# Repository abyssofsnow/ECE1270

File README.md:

# ECE1270

555 Timer Project built using Eagle Software

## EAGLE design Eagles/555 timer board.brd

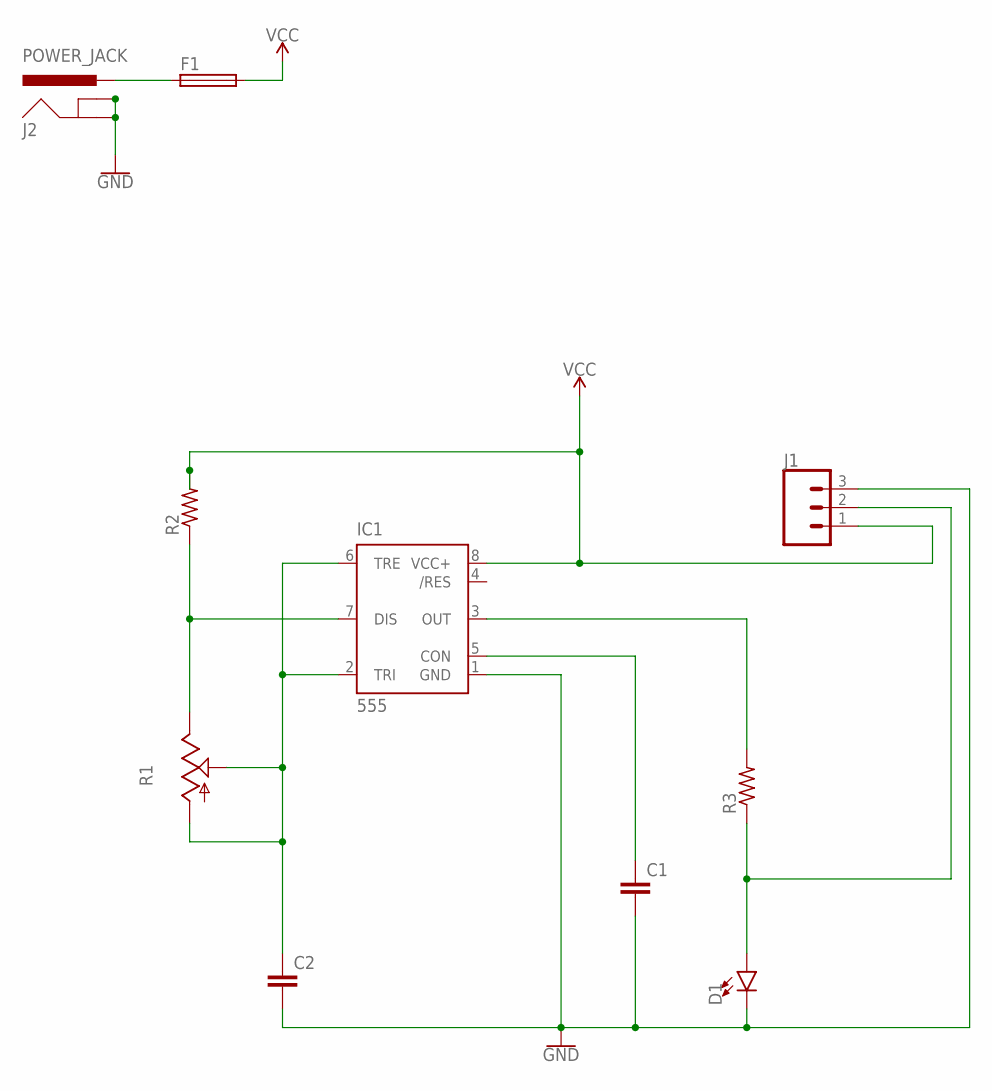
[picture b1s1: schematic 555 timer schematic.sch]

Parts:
C1: C7.5/3; C7.5B3
C2: C15/5; C15B5
D1: LED5MM; LED_5MM
F1: SH22
IC1: 555; DIP08
J1: CONN_03; 1X03
J2: POWER_JACK; POWER_JACK_PTH
R1: TRIM_US-CA6V; CA6V
R2: R-US_R1210; R1210
R3: R-US_0207/12; 0207/12

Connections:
GND: C1.2, C2.2, D1.K (C), IC1.1 (GND), J1.3
unnamed: F1.1, J2.PWR
unnamed: J2.GND, J2.GNDBREAK
unnamed: C2.1, IC1.2 (TRI), IC1.6 (TRE), R1.A, R1.S
unnamed: IC1.7 (DIS), R1.E, R2.1
unnamed: C1.1, IC1.5 (CON)
unnamed: D1.A, J1.2, R3.1
unnamed: IC1.3 (OUT), R3.2
VCC: F1.2, IC1.8 (VCC+), J1.1, R2.2

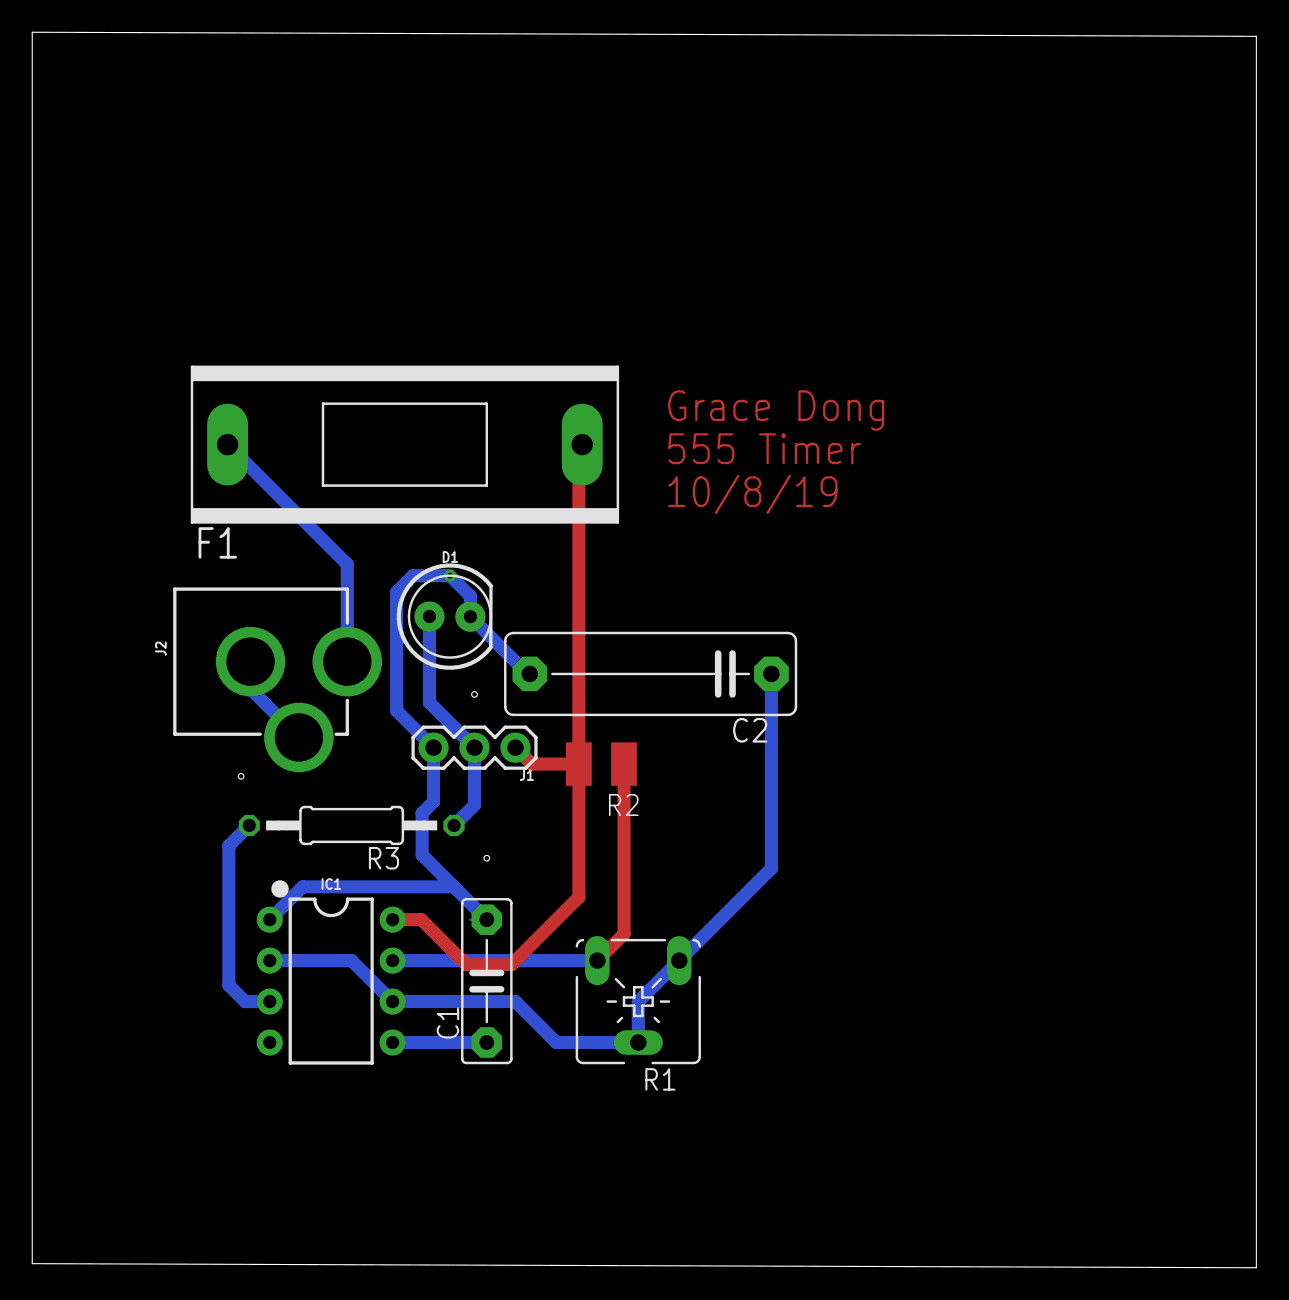
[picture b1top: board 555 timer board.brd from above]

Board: 2 copper layers, 75.9 x 76.6 mm, 10 parts (0 on the bottom side), 9 nets.

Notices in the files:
parts and their libraries:
SparkFun-LED: Licensing: Creative Commons ShareAlike 4.0 International - https://creativecommons.org/licenses/by-sa/4.0
